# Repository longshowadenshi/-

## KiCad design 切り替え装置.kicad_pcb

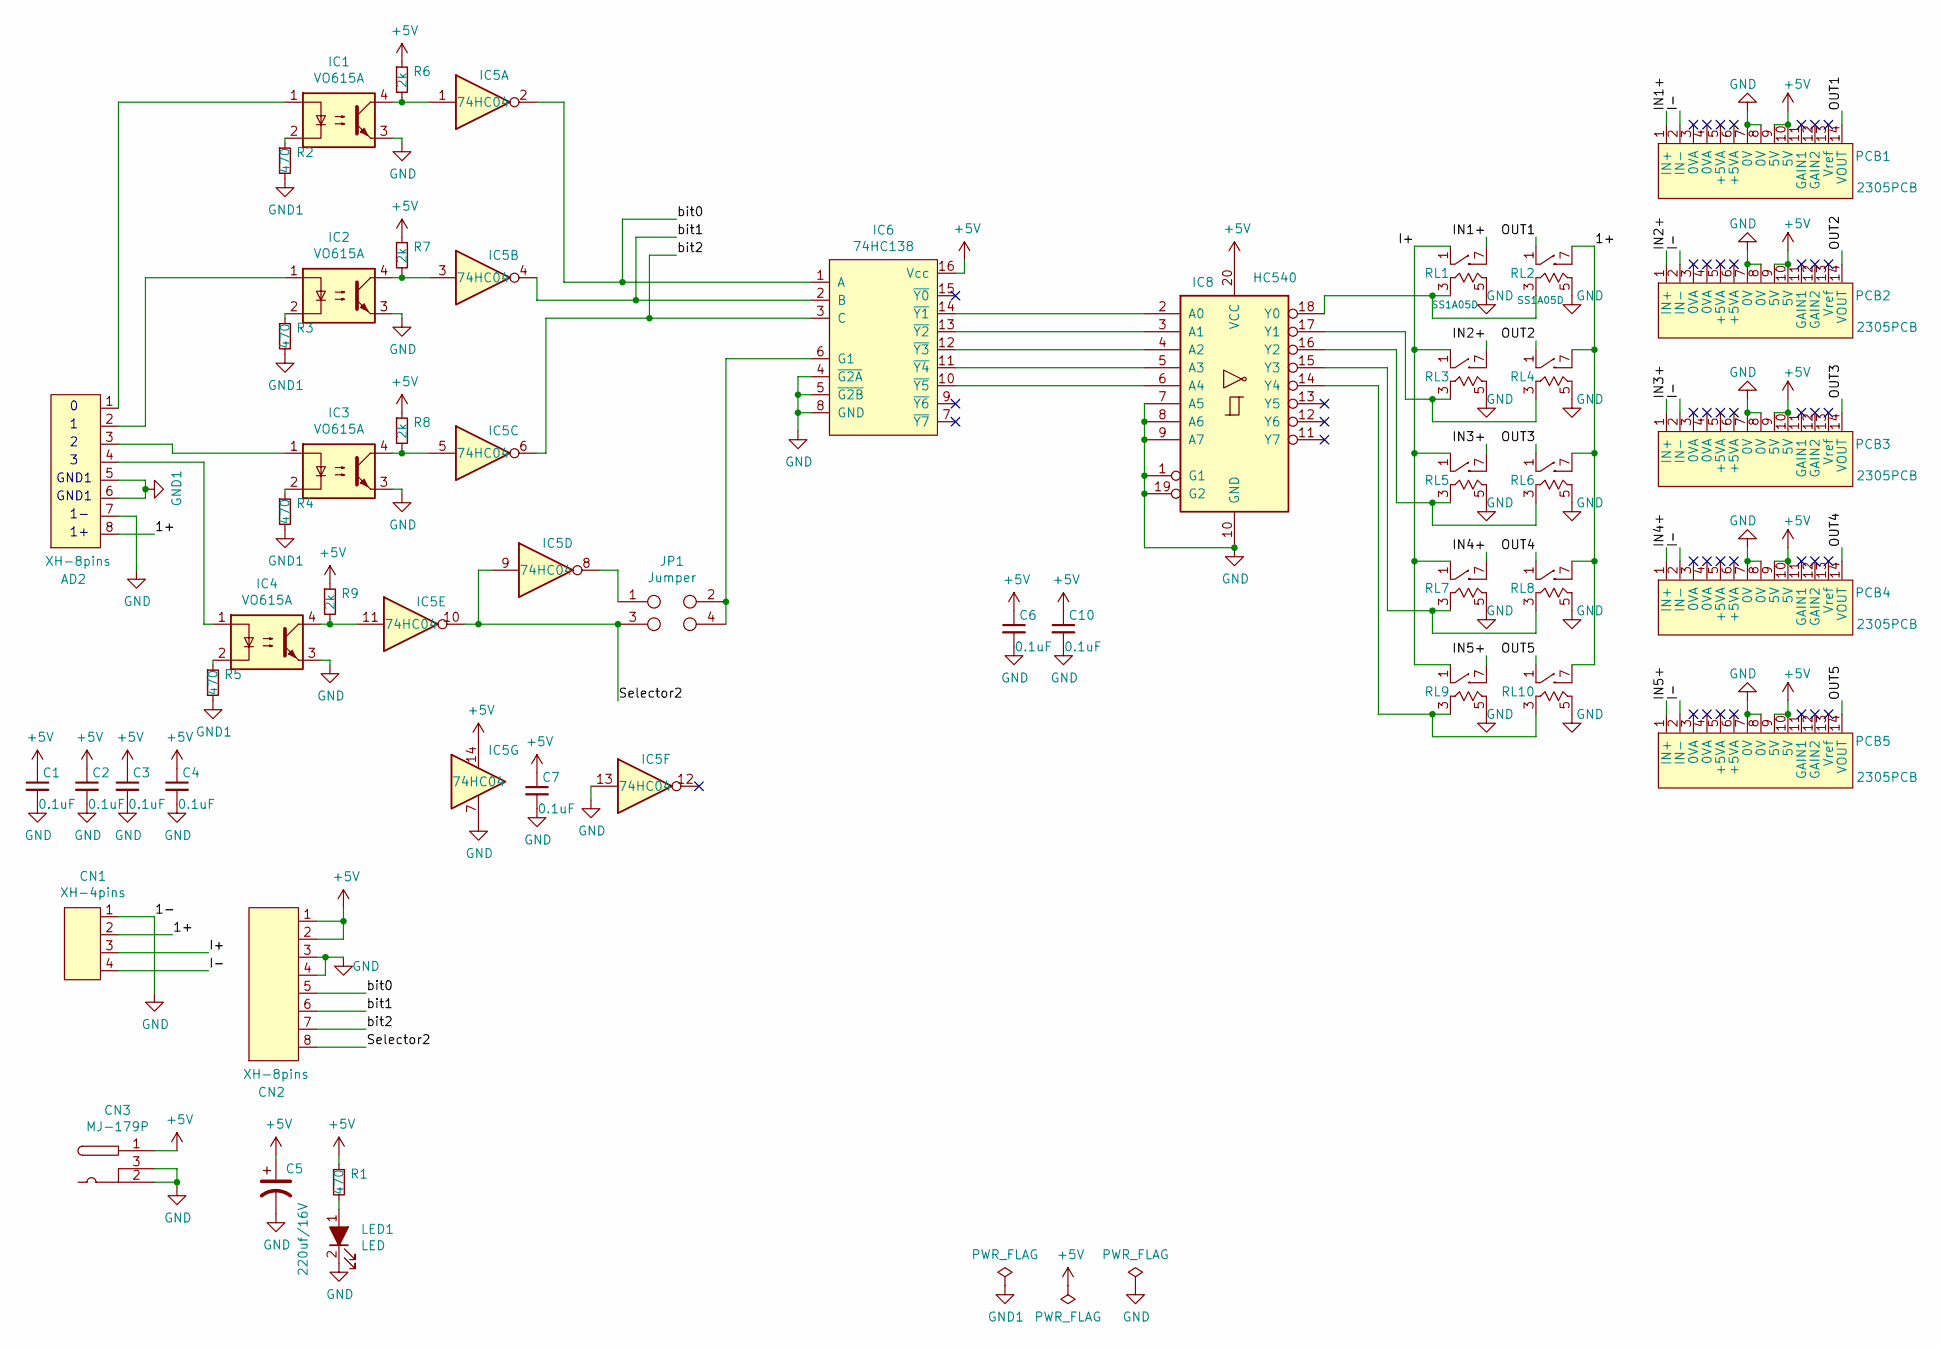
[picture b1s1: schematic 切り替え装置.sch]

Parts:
AD2: XH-8pins; cn_B8B-XH-A
C1, C2, C3, C4, C6, C7, C10: 0.1uF; 0.1uf-bypass
C5: 220uf/16V; 220uF-16V
CN1: XH-4pins; cn_B4B-XH-A
CN2: XH-8pins; cn_B8B-XH-A
CN3: MJ-179P; MJ179P
IC1, IC2, IC3, IC4: VO615A; VO618A-4
IC5: 74HC04; 74HC-14pins
IC6: 74HC138; 74HC-16pins
IC8: HC540; 74HC-20pins
JP1: Jumper; jumper
LED1: LED; led-os
PCB1, PCB2, PCB3, PCB4, PCB5: 2305PCB; 2305基板
R1, R2, R3, R4, R5: 470; R
R6, R7, R8, R9: 2k; R
RL1, RL2, RL3, RL4, RL5, RL6, RL7, RL8, RL9, RL10: SS1A05D

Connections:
+5V: C1.1, C2.1, C3.1, C4.1, C5.1, C6.1, C7.1, C10.1, CN2.1, CN2.2, CN3.1, IC5.14, IC6.16 (Vcc), IC8.20 (VCC), PCB1.9 (5V), PCB1.10 (5V), PCB2.9 (5V), PCB2.10 (5V), PCB3.9 (5V), PCB3.10 (5V), PCB4.9 (5V), PCB4.10 (5V), PCB5.9 (5V), PCB5.10 (5V), R1.1, R6.1, R7.1, R8.1, R9.1
/1+: AD2.8, CN1.2, RL2.7, RL4.7, RL6.7, RL8.7, RL10.7
/I+: CN1.3, RL1.1, RL3.1, RL5.1, RL7.1, RL9.1
/I-: CN1.4, PCB1.2 (IN-), PCB2.2 (IN-), PCB3.2 (IN-), PCB4.2 (IN-), PCB5.2 (IN-)
/IN1+: PCB1.1 (IN+), RL1.7
/IN2+: PCB2.1 (IN+), RL3.7
/IN3+: PCB3.1 (IN+), RL5.7
/IN4+: PCB4.1 (IN+), RL7.7
/IN5+: PCB5.1 (IN+), RL9.7
/OUT1: PCB1.14 (VOUT), RL2.1
/OUT2: PCB2.14 (VOUT), RL4.1
/OUT3: PCB3.14 (VOUT), RL6.1
/OUT4: PCB4.14 (VOUT), RL8.1
/OUT5: PCB5.14 (VOUT), RL10.1
/Selector2: CN2.8, IC5.9, IC5.10, JP1.3
/bit0: CN2.5, IC5.2, IC6.1 (A)
/bit1: CN2.6, IC5.4, IC6.2 (B)
/bit2: CN2.7, IC5.6, IC6.3 (C)
GND: AD2.7, C1.2, C2.2, C3.2, C4.2, C5.2, C6.2, C7.2, C10.2, CN1.1, CN2.3, CN2.4, CN3.2, CN3.3, IC1.3, IC2.3, IC3.3, IC4.3, IC5.7, IC5.13, IC6.4 (~G2A), IC6.5 (~G2B), IC6.8 (GND), IC8.1 (G1), IC8.7 (A5), IC8.8 (A6), IC8.9 (A7), IC8.10 (GND), IC8.19 (G2), LED1.2, PCB1.7 (0V), PCB1.8 (0V), PCB2.7 (0V), PCB2.8 (0V), PCB3.7 (0V), PCB3.8 (0V), PCB4.7 (0V), PCB4.8 (0V), PCB5.7 (0V), PCB5.8 (0V), RL1.5, RL2.5, RL3.5, RL4.5, RL5.5, RL6.5, RL7.5, RL8.5, RL9.5, RL10.5
GND1: AD2.5, AD2.6, R2.2, R3.2, R4.2, R5.2
unnamed: AD2.1, IC1.1
unnamed: AD2.2, IC2.1
unnamed: AD2.3, IC3.1
unnamed: AD2.4, IC4.1
unnamed: IC1.2, R2.1
unnamed: IC1.4, IC5.1, R6.2
unnamed: IC2.2, R3.1
unnamed: IC2.4, IC5.3, R7.2
unnamed: IC3.2, R4.1
unnamed: IC3.4, IC5.5, R8.2
unnamed: IC4.2, R5.1
unnamed: IC4.4, IC5.11, R9.2
unnamed: IC5.8, JP1.1
unnamed: IC6.6 (G1), JP1.2, JP1.4
unnamed: IC6.10 (~Y5), IC8.6 (A4)
unnamed: IC6.11 (~Y4), IC8.5 (A3)
unnamed: IC6.12 (~Y3), IC8.4 (A2)
unnamed: IC6.13 (~Y2), IC8.3 (A1)
unnamed: IC6.14 (~Y1), IC8.2 (A0)
unnamed: IC8.14 (Y4), RL9.3, RL10.3
unnamed: IC8.15 (Y3), RL7.3, RL8.3
unnamed: IC8.16 (Y2), RL5.3, RL6.3
unnamed: IC8.17 (Y1), RL3.3, RL4.3
unnamed: IC8.18 (Y0), RL1.3, RL2.3
unnamed: LED1.1, R1.2

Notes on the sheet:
GND1

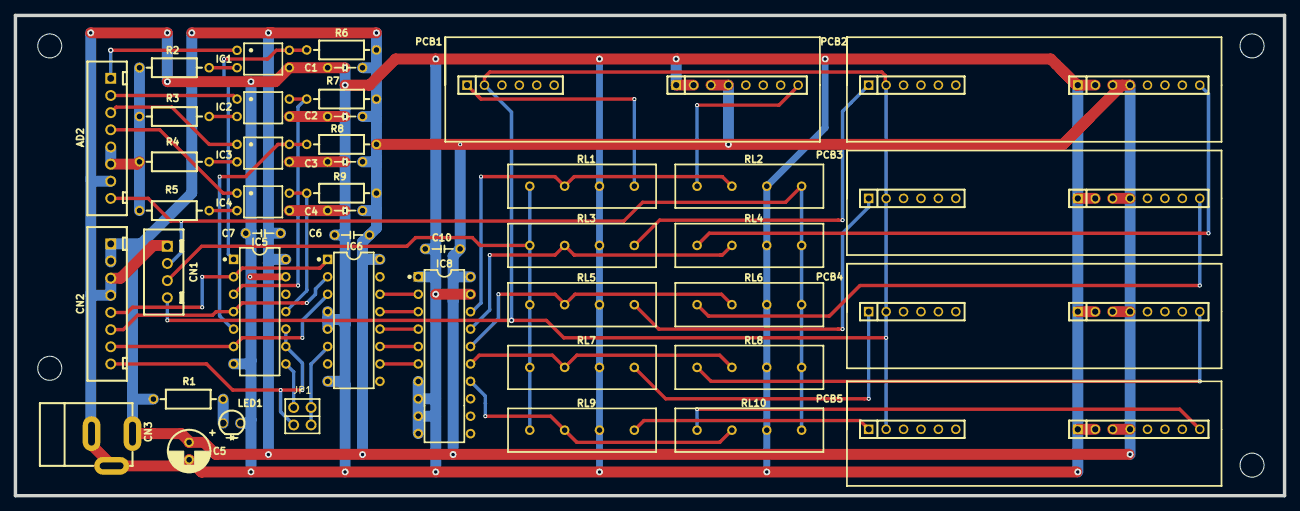
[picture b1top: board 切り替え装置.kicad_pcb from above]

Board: 2 copper layers, 185.0 x 70.0 mm, 45 parts (0 on the bottom side), 45 nets.
